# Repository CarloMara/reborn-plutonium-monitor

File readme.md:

**Introduction**

Reborn Plutoniom Monitor is a small project born from the idea of having the possibility to carry a second monitor around. FYI I'm a student and I move around the city a lot. There are other option in the market that could suit my needs, but they are mostly based off USB, which I imagine would be a pain to get working on linux.

The project is based off a 14 inch laptop display that can be easly found on common on-line stores as spare.

*Things done so far*

I've just designed a first test board with all of the connections from the display's flat cable broken out, so it should be a little easier to test whether or not the pinout of the panel is correct. 

-----------------------------------------------------------------------------------------------------------------------------------------------------------

**Brief Display Info**

The display I have choose it's not very new, but thanks to it's age a datasheet for it is easily repairable.

I've also chosen this display because it's has all the back-lighting control electronic integrated, saving a big hassle. 

----------------------------------------------------------------------------------------------------------------------------------------------------------

**Possible Development Path**

I have bought all the components needed to build the test board , but I still need to find some time to etch a pcb, and try it out.

In the future I plan to make a bigger board, maybe with a 4.0 ble chip in order to control the brightness and get the battery status to the host pc.

Of course this means designing a solution to charge the battery, maybe using USB-PD, but right now I don't have any time for that.

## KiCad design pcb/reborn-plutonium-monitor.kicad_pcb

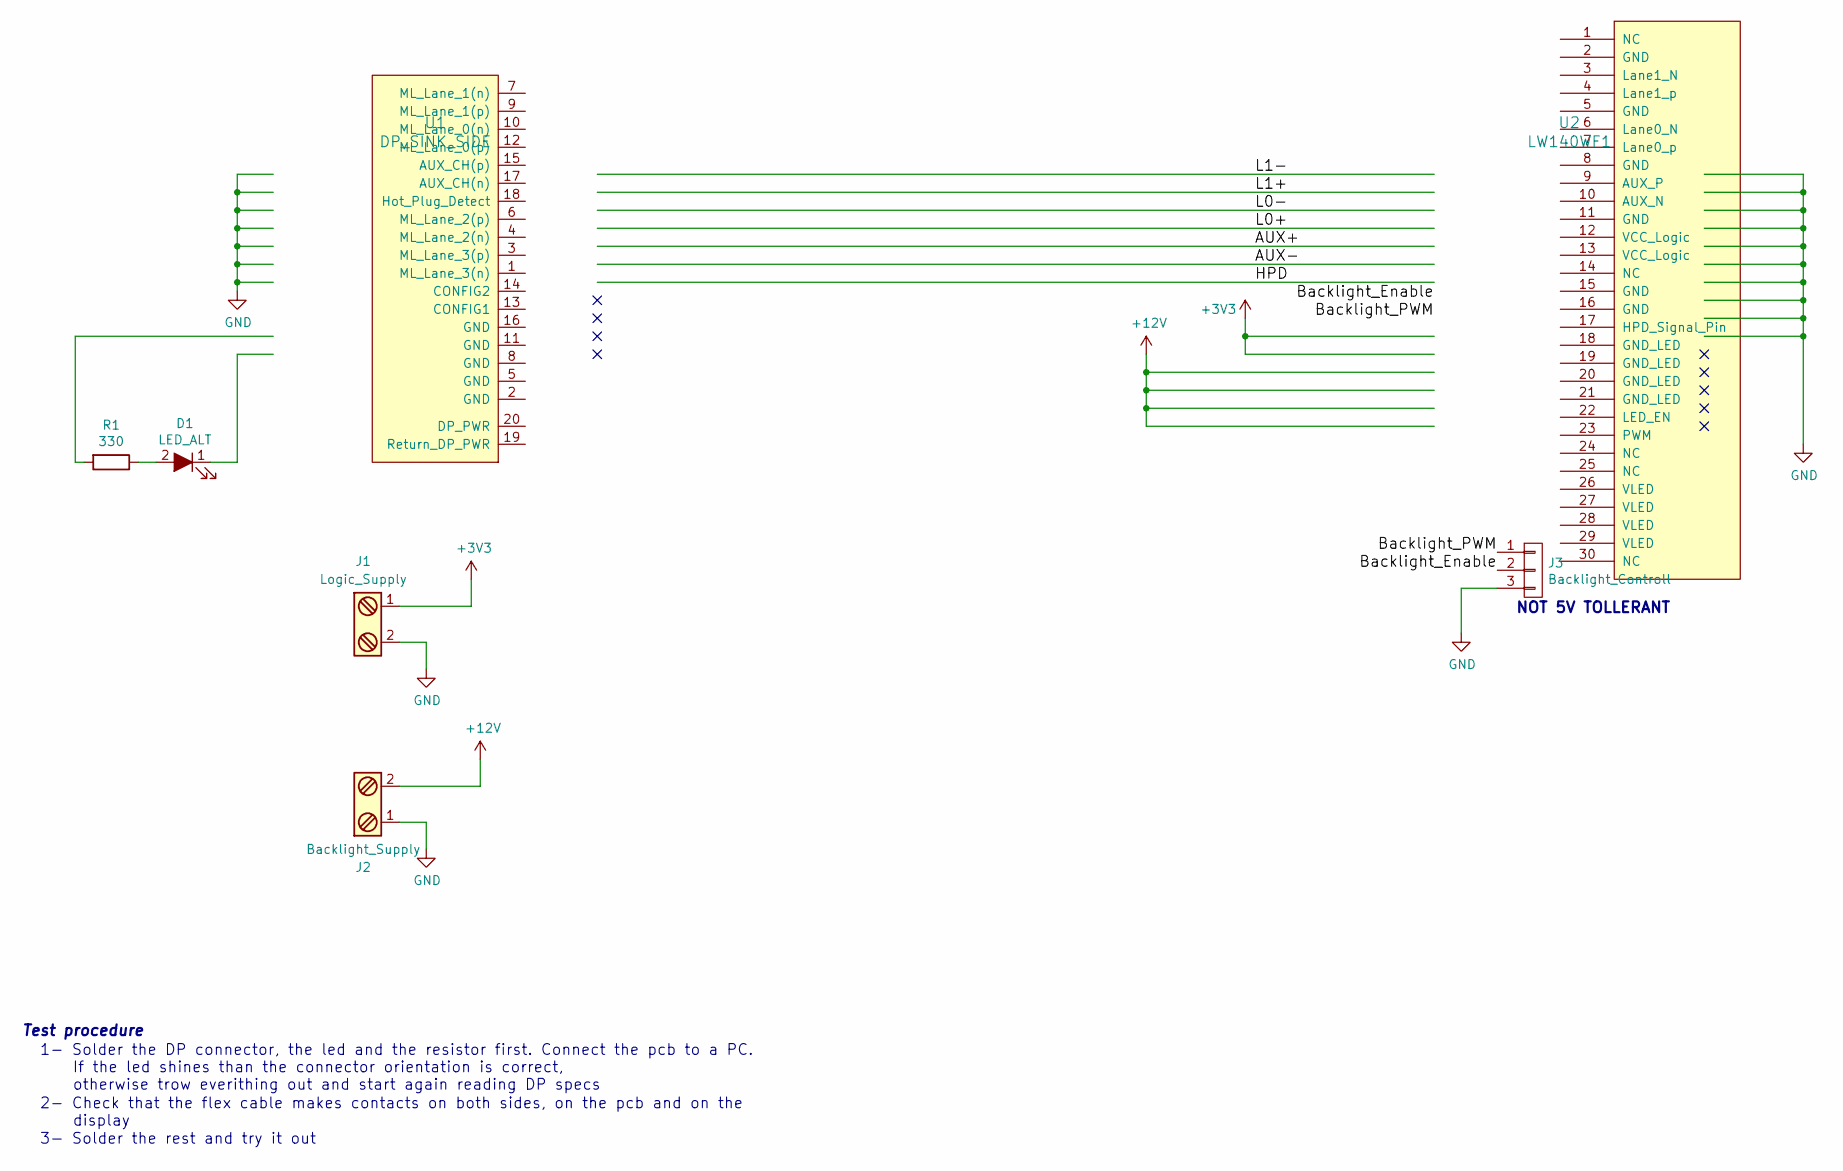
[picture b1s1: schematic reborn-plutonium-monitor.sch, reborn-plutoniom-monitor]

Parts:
D1: LED_ALT; R_1206_HandSoldering
J1: Logic_Supply; TerminalBlock_Pheonix_MPT-2.54mm_2pol
J2: Backlight_Supply; TerminalBlock_Pheonix_MPT-2.54mm_2pol
J3: Backlight_Controll; Pin_Header_Straight_1x03_Pitch2.54mm
R1: 330; R_1206_HandSoldering
U1: DP_SINK_SIDE; 2040210-1
U2: LW140WF1; F0500WR-S-30PT

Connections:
+3V3: J1.1, U2.12 (VCC_Logic), U2.13 (VCC_Logic)
+12V: J2.2, U2.26 (VLED), U2.27 (VLED), U2.28 (VLED), U2.29 (VLED)
/AUX+: U1.15 (AUX_CH(p)), U2.9 (AUX_P)
/AUX-: U1.17 (AUX_CH(n)), U2.10 (AUX_N)
/Backlight_Enable: J3.2, U2.22 (LED_EN)
/Backlight_PWM: J3.1, U2.23 (PWM)
/HPD: U1.18 (Hot_Plug_Detect), U2.17 (HPD_Signal_Pin)
/L0+: U1.12 (ML_Lane_0(p)), U2.7 (Lane0_p)
/L0-: U1.10 (ML_Lane_0(n)), U2.6 (Lane0_N)
/L1+: U1.9 (ML_Lane_1(p)), U2.4 (Lane1_p)
/L1-: U1.7 (ML_Lane_1(n)), U2.3 (Lane1_N)
GND: J1.2, J2.1, J3.3, U1.2 (GND), U1.5 (GND), U1.8 (GND), U1.11 (GND), U1.13 (CONFIG1), U1.14 (CONFIG2), U1.16 (GND), U2.2 (GND), U2.5 (GND), U2.8 (GND), U2.11 (GND), U2.15 (GND), U2.16 (GND), U2.18 (GND_LED), U2.19 (GND_LED), U2.20 (GND_LED), U2.21 (GND_LED)
unnamed: D1.1 (K), U1.19 (Return_DP_PWR)
unnamed: D1.2 (A), R1.1
unnamed: R1.2, U1.20 (DP_PWR)

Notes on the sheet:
Test procedure
1- Solder the DP connector, the led and the resistor first. Connect the pcb to a PC. If the led shines than the connector orientation is correct, otherwise trow everithing out and start again reading DP specs
2- Check that the flex cable makes contacts on both sides, on the pcb and on the display
3- Solder the rest and try it out
NOT 5V TOLLERANT

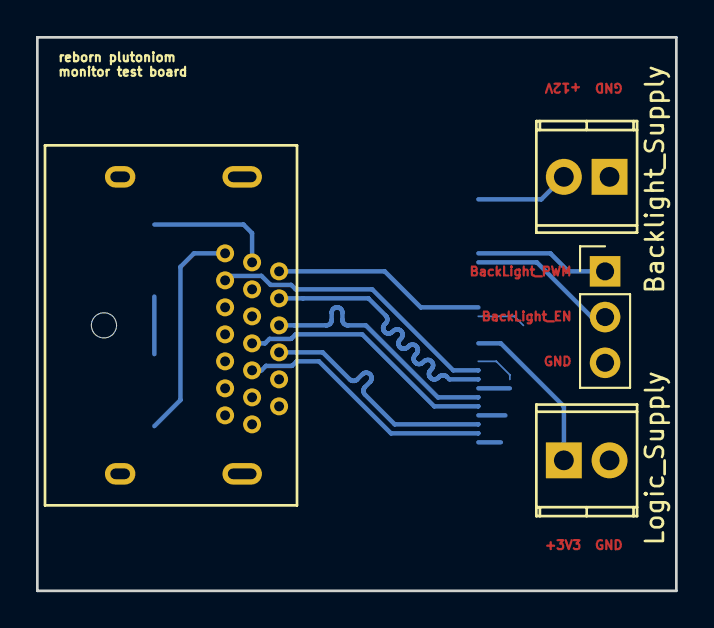
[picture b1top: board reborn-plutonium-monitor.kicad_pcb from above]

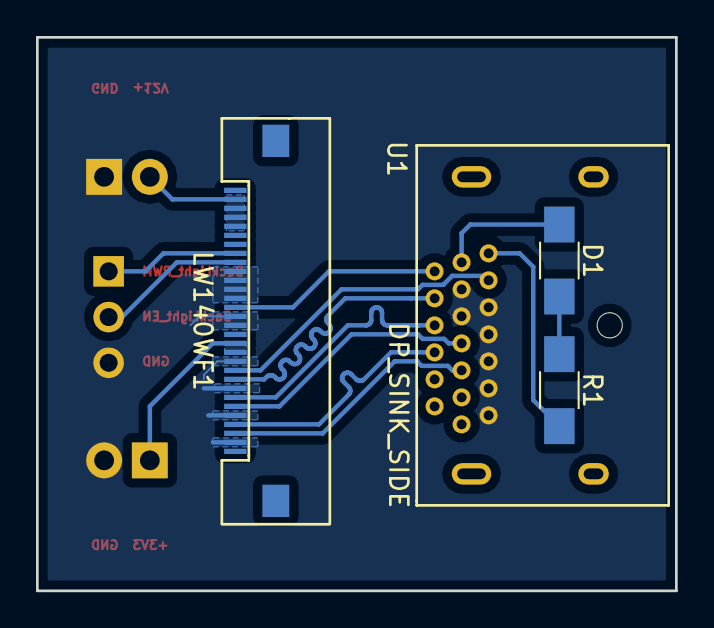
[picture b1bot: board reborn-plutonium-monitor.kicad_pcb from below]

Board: 2 copper layers, 35.5 x 30.8 mm, 7 parts (3 on the bottom side), 15 nets.

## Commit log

2017-04-03 added readme
